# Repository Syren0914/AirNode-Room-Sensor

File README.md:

# AirNode Room Sensor

> [!WARNING]
> **AirNode is an ongoing, unfinished prototype.** The PCB, enclosure, firmware, pin assignments, and documentation may change. This revision has not completed long-term validation, calibration, or product safety testing and is not production ready.

AirNode is an ESP32-C3 based indoor air-quality monitor in a compact 70 mm × 100 mm enclosure. It combines a round color display, four buttons, an audible alarm, and connections for environmental sensor modules.

## Current capabilities

- ESP32-C3 SuperMini with Wi-Fi and Bluetooth LE
- 1.28-inch round SPI TFT
- SHT40 temperature and humidity sensor
- SCD40 carbon-dioxide sensor connection
- SGP41 VOC and NOx sensor connection
- SPS30 particulate-matter sensor connection
- Back-mounted passive piezo buzzer on GPIO20
- Four buttons: Up, Down, Select, and Back
- Two-layer 70 mm × 100 mm PCB with 8 mm corner radii
- 3D-printable enclosure source

## Project status

This repository records a working prototype and the next custom PCB revision. The photographed device uses development modules and point-to-point wiring; the KiCad design consolidates those connections onto a PCB.

| Area | Status |
| --- | --- |
| Schematic ERC | Pass: 0 violations |
| PCB connectivity | Pass: 0 unconnected items |
| PCB DRC | Pass: 0 violations and 0 unconnected pads |
| Enclosure | Prototype printed and assembled; PCB fit still requires physical verification |
| Firmware | Working prototype shown; source has not been added to this repository yet |
| Sensor calibration | In progress |
| Production testing | Not started |

## Documentation

- [Hardware and pin assignments](docs/HARDWARE.md)
- [Assembly guide](docs/ASSEMBLY.md)
- [First power-on and validation](docs/BRINGUP.md)
- [Firmware status and requirements](docs/FIRMWARE.md)
- [Enclosure and mechanical fit](docs/ENCLOSURE.md)
- [Board-mounted USB-C power input](docs/USB-C-extension.md)
- [Manufacturing audit](docs/MANUFACTURING-AUDIT.md)
- [Bill of materials](BOM.csv)
- [Change log](CHANGELOG.md)

## Repository contents

- `Room Sensor.kicad_pro` — KiCad project
- `Room Sensor.kicad_sch` — schematic source
- `Room Sensor.kicad_pcb` — PCB layout source
- `RoomSensor_Libraries/` — project symbols and footprints
- `V.2.3mf` — printable enclosure source
- `Room Sensor.step` — PCB 3D export
- `BOM.csv` — bill of materials
- `manufacturing/gerbers/` — fabrication outputs for the current revision

Open `Room Sensor.kicad_pro` with KiCad 10 or newer. Review the schematic, PCB, and fabrication files together before ordering boards because the project remains under development.

## Prototype gallery

### Assembled enclosure

### Working development prototype

### Internal development build

These photos show development wiring and module placement. They do not represent the final PCB assembly.

| Open prototype | Assembly in progress |
| --- | --- |
|  |  |

## Enclosure files

[Download `V.2.3mf`](V.2.3mf)

## Before building

1. Read the [hardware notes](docs/HARDWARE.md) and confirm that your modules match the listed pin order and voltage.
2. Verify the exact dimensions and pad spacing of every purchased breakout board. Visually similar modules often differ.
3. Inspect the fabrication files and run ERC and DRC with your installed KiCad version.
4. Assemble and test one prototype before ordering multiple boards.
5. Follow the staged checks in the [bring-up guide](docs/BRINGUP.md).

## License

Hardware design files are released under the CERN Open Hardware Licence Version 2 — Strongly Reciprocal. See [LICENSE](LICENSE).

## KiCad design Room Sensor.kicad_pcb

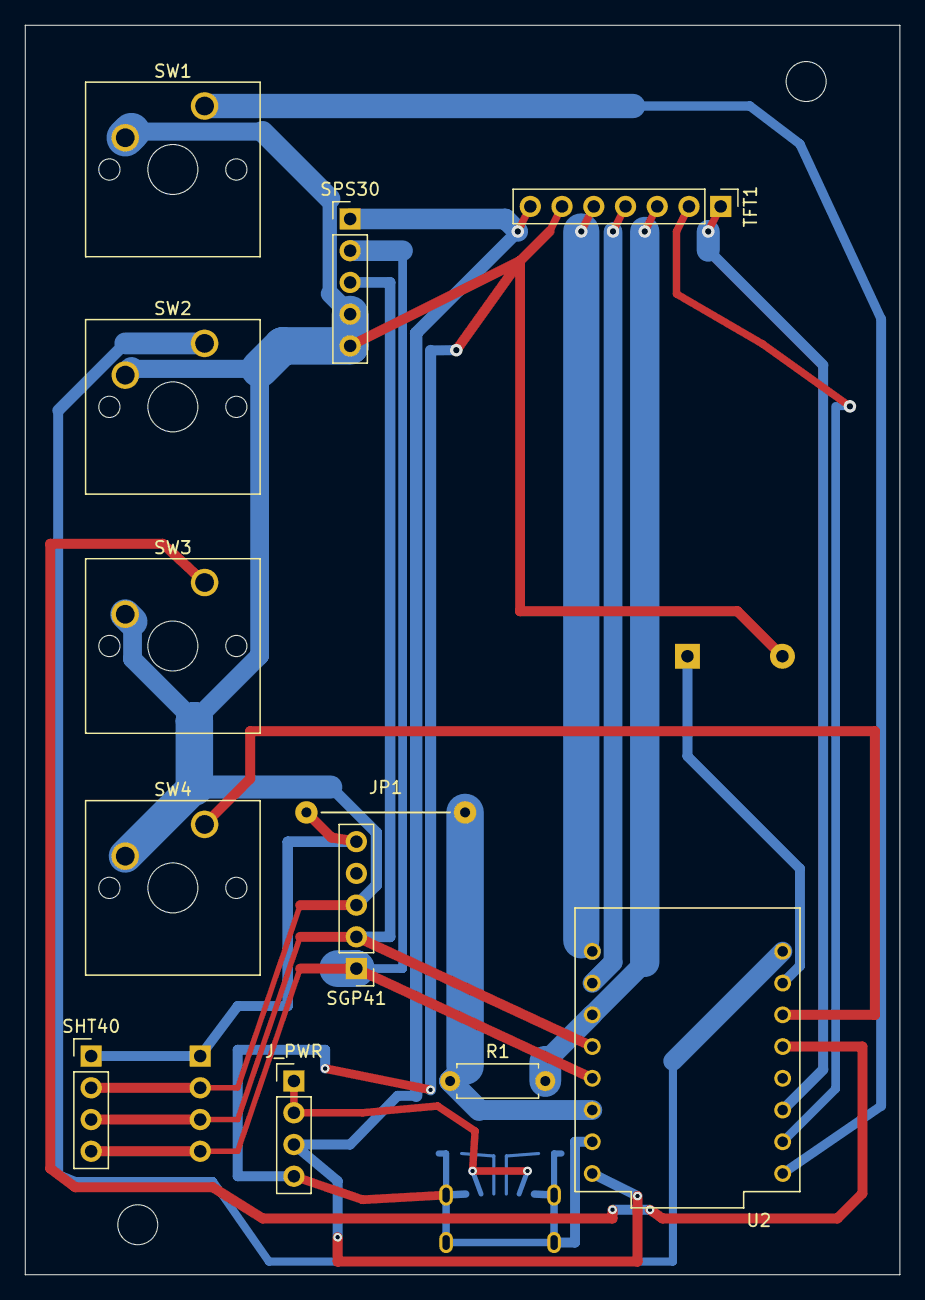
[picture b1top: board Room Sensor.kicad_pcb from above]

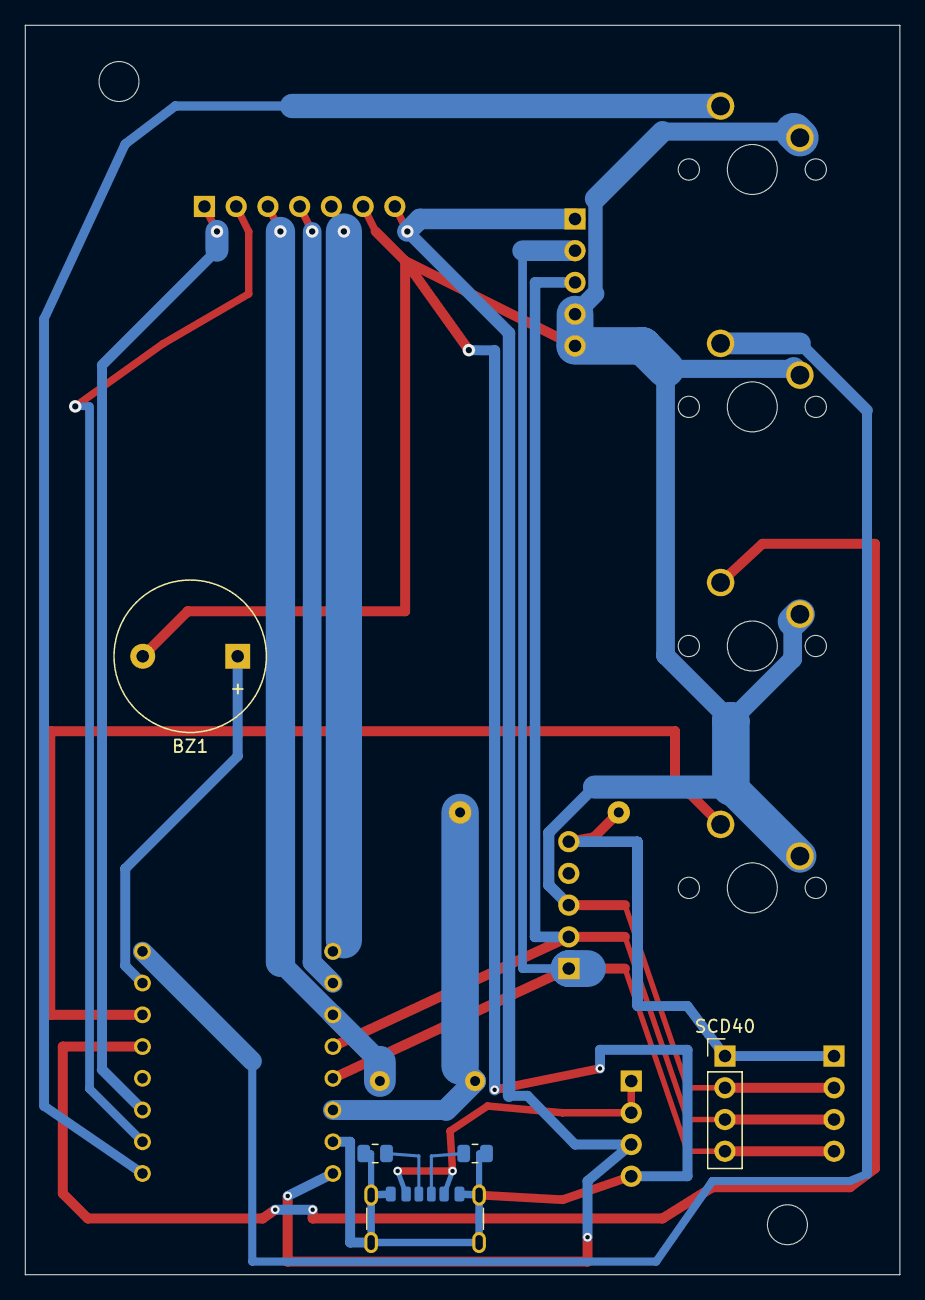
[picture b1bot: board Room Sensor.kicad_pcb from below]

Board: 2 copper layers, 70.0 x 100.0 mm, 19 parts (6 on the bottom side), 19 nets.

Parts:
BZ1: Piezo Buzzer; Buzzer_12x9.5RM7.6
H1, H2: MountingHole_3.2mm_M3
JP1: INSULATED WIRE; Wire_Link_P12.70mm
J_PWR: USB5V_SW_COM_SW_NO_GND; PinHeader_1x04_P2.54mm_Vertical
J_USB: GCT USB4125-GF-A (1.00 mm shell stake); USB_C_Receptacle_GCT_USB4125-xx-x_6P_TopMnt_Horizontal
R1: 10k; R_Axial_DIN0207_L6.3mm_D2.5mm_P7.62mm_Horizontal
R_CC1, R_CC2: 5.1k; R_0805_2012Metric
SCD40: SCD40 I2C; PinHeader_1x04_P2.54mm_Vertical
SGP41: Conn_01x05; PinHeader_1x05_P2.54mm_Vertical
SHT40: Conn_01x04; PinHeader_1x04_P2.54mm_Vertical
SPS30: Conn_01x05; PinHeader_1x05_P2.54mm_Vertical
SW1, SW2, SW3, SW4: SW_Push; SW_Cherry_MX_1.00u_PCB
TFT1: Conn_01x07; PinHeader_1x07_P2.54mm_Vertical
U2: ESP32-C3_SUPERMINI_TH; MODULE_ESP32-C3_SUPERMINI_TH

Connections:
/BTN_BACK: SW4.1, U2.10 (GPIO10)
/BTN_DOWN: SW2.1, U2.21 (GPIO21)
/BTN_SELECT: SW3.1, U2.9 (GPIO9)
/BTN_UP: SW1.1, U2.5 (GPIO5)
/BUZZER: BZ1.1, U2.20 (GPIO20)
/CS: TFT1.2, U2.6 (GPIO6)
/DC: R1.2, TFT1.3, U2.2 (GPIO2)
/GND: BZ1.2, J_PWR.4, J_USB.A12, J_USB.B12, J_USB.SH, R_CC1.2, R_CC2.2, SCD40.2, SGP41.3, SHT40.2, SPS30.4, SPS30.5, SW1.2, SW2.2, SW3.2, SW4.2, TFT1.6, U2.G (GND)
/RST: TFT1.1, U2.7 (GPIO7)
/SCL: SCD40.3, SGP41.2, SHT40.3, SPS30.3, U2.3 (GPIO3)
/SDA: SCD40.4, SGP41.1, SHT40.4, SPS30.2, U2.4 (GPIO4)
/SENSOR_3V3: JP1.1, SCD40.1, SGP41.5, SHT40.1
/TFT_SCL: TFT1.5, U2.0 (GPIO0)
/TFT_SDA: TFT1.4, U2.1 (GPIO1)
/USB_CC1: J_USB.A5, R_CC1.1
/USB_CC2: J_USB.B5, R_CC2.1
/USB_VBUS_RAW: J_PWR.1, J_PWR.2, J_USB.A9, J_USB.B9
/VCC (3.3v): JP1.2, R1.1, U2.3.3 (3V3)
/VIN (5.0v): J_PWR.3, SPS30.1, TFT1.7, U2.5V
